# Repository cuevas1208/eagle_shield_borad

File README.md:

# eagle_shield_borad
Learning to do a shield board with eagle

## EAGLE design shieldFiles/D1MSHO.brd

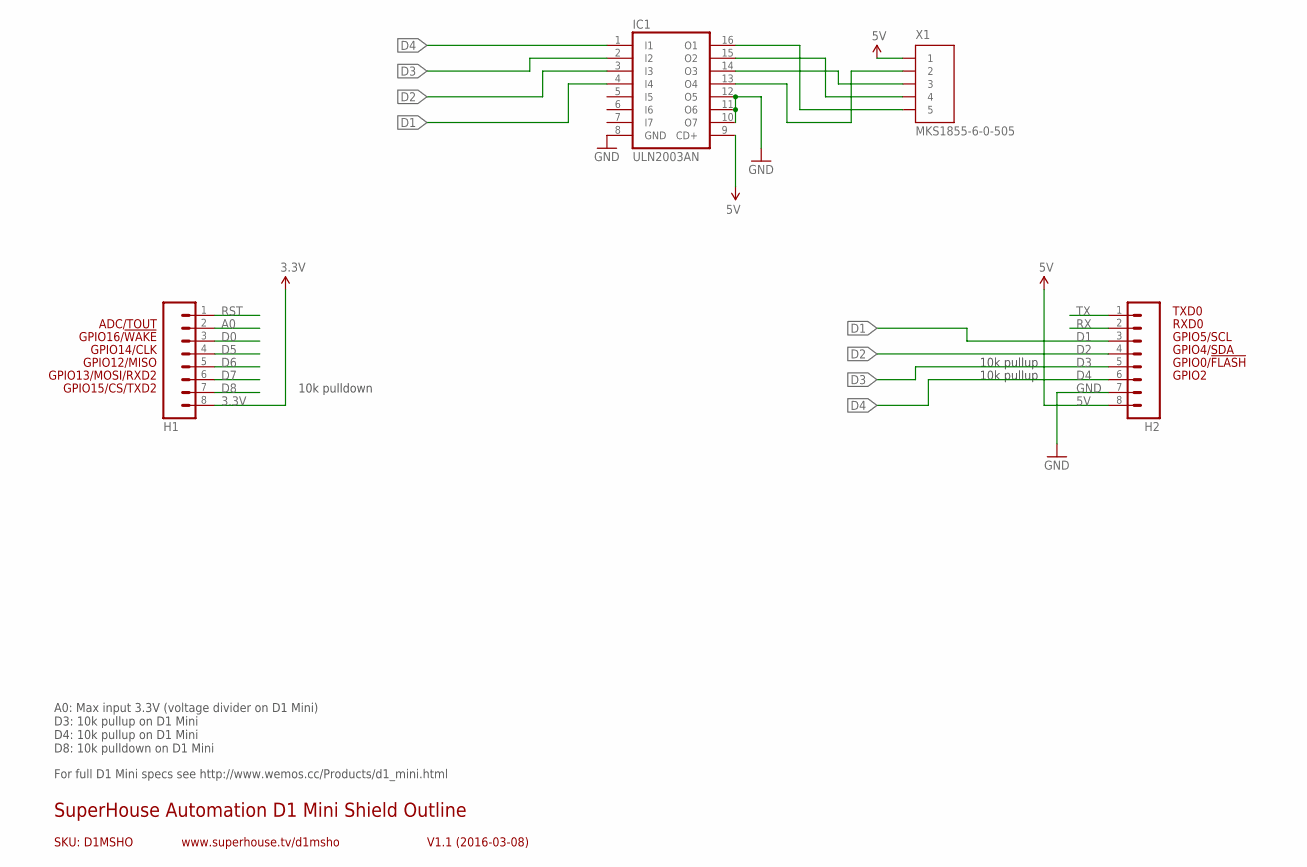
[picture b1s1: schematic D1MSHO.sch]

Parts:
H1, H2: M08; 1X08
IC1: ULN2003AN; DIL16
X1: MKS1855-6-0-505

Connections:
3.3V: H1.8
5V: H2.8, IC1.9 (CD+), X1.1
A0: H1.2
D0: H1.3
D1: H2.3, IC1.4 (I4)
D2: H2.4, IC1.3 (I3)
D3: H2.5, IC1.2 (I2)
D4: H2.6, IC1.1 (I1)
D5: H1.4
D6: H1.5
D7: H1.6
D8: H1.7
GND: H2.7, IC1.8 (GND), IC1.10 (O7), IC1.11 (O6), IC1.12 (O5)
unnamed: IC1.16 (O1), X1.5
unnamed: IC1.15 (O2), X1.4
unnamed: IC1.14 (O3), X1.3
unnamed: IC1.13 (O4), X1.2
RST: H1.1
RX: H2.2
TX: H2.1

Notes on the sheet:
GPIO2
GPIO0/!FLASH
GPIO12/MISO
GPIO4/SDA
GPIO5/SCL
RXD0
TXD0
GPIO13/MOSI/RXD2
GPIO14/CLK
GPIO15/CS/TXD2
GPIO16/!WAKE
SKU: D1MSHO
SuperHouse Automation D1 Mini Shield Outline
V1.1 (2016-03-08)
www.superhouse.tv/d1msho
ADC/TOUT
A0: Max input 3.3V (voltage divider on D1 Mini) D3: 10k pullup on D1 Mini D4: 10k pullup on D1 Mini D8: 10k pulldown on D1 Mini
10k pulldown
10k pullup
For full D1 Mini specs see http://www.wemos.cc/Products/d1_mini.html

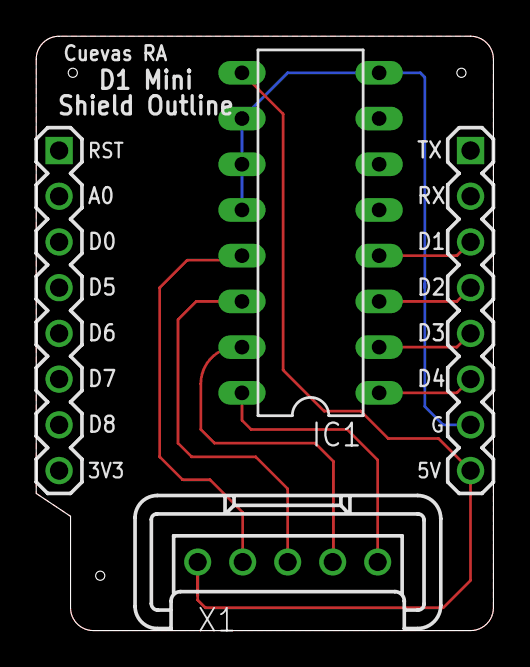
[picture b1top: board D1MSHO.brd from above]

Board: 2 copper layers, 25.4 x 33.0 mm, 4 parts (0 on the bottom side), 10 nets.

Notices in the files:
parts and their libraries:
freetronics-original: Licensing: CC v3.0 Share-Alike You are welcome to use this library for commercial purposes.
